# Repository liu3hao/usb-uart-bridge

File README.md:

# Compact CH340 USB-C USB-UART bridge
This repository contains the files for a compact USB-C to UART bridge using the CH340 chip. The main purpose is to create a compact dev board that can be used for UART communications.

## Project files
1. Schematics - designed with [circuitscript](https://circuitscript.net)
2. PCB layout - designed with [KiCad](https://www.kicad.org/)

## Production
The initial production was done with [JLCPCB](https://jlcpcb.com/) and parts are completely sourced from LCSC.

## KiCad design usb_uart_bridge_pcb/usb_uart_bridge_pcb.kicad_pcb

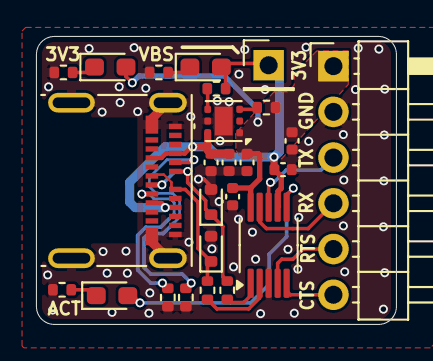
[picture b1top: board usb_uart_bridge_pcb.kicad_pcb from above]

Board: 2 copper layers, 20.0 x 16.0 mm, 25 parts (0 on the bottom side), 19 nets.

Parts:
C1, C2, C3, C4: 100n; C_0402_1005Metric
C5, C6: 1u; C_0402_1005Metric
D1, D2: D_SOD-523
D3, D4, D5: LED_0603_1608Metric_Pad1.05x0.95mm_HandSolder
J1: USB_C_Receptacle_Molex_105450-0101
J2: PinHeader_1x06_P2.54mm_Horizontal
J3: PinHeader_1x01_P2.54mm_Vertical
R1, R2: 0; R_0402_1005Metric
R3, R4, R5, R6, R7, R8, R9: 5.1k; R_0402_1005Metric
U1: MSOP-10_3x3mm_P0.5mm
U2: WSON-6-1EP_2x2mm_P0.65mm_EP1x1.6mm_ThermalVias

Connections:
/3V3: C3.1, C4.1, C6.1, D4.2, J2.1, R5.1, U1.10, U2.1
/CTS#: J2.6, U1.5
/D+: D1.1, J1.A6, J1.B6, R1.1
/D-: D2.1, J1.A7, J1.B7, R2.1
/GND: C1.2, C2.2, C3.2, C4.2, C5.2, C6.2, D1.2, D2.2, J1.A1, J1.A12, J1.B1, J1.B12, J1.S1, J2.2, R3.2, R6.2, R7.2, R8.2, R9.2, U1.3, U2.5, U2.7
/NET-(D3-1): D3.1, R3.1
/NET-(D4-1): D4.1, R6.1
/NET-(D5-1): D5.1, R7.1
/NET-(J1-A5): J1.A5, R8.1
/NET-(J1-B5): J1.B5, R9.1
/NET-(R1-2): R1.2, U1.1
/NET-(R2-2): R2.2, U1.2
/NET-(R4-2): R4.2, U2.4
/NET-(R5-2): R5.2, U2.3
/RTS#: J2.5, U1.4
/RXD: J2.4, U1.9
/TNOW: D3.2, U1.6
/TXD: J2.3, U1.8
/VBUS: C1.1, C2.1, C5.1, D5.2, J1.A4, J1.A9, J1.B4, J1.B9, J3.1, R4.1, U1.7, U2.6

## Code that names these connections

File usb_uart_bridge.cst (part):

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                to connheader_6pins pin 4

            "RTS#":
                add label("RTS#")
                wire auto
                to connheader_6pins pin 5

            "CTS#":
                add label("CTS#")
                wire auto
                to connheader_6pins pin 6
            
            "TNOW": 
                add label("TNOW")
                wire right 200
                wire down 100
                add led("RED") pin 2 #= D3 
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
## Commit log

2025-10-05 1. initial commit
2025-10-07 1. fixed missing 5.1K resistors
2026-01-11 1. added refdes comments 2. added parameter assignment rules
2026-01-11 1. added license
2026-01-11 1.added README and output schematic in pdf format
